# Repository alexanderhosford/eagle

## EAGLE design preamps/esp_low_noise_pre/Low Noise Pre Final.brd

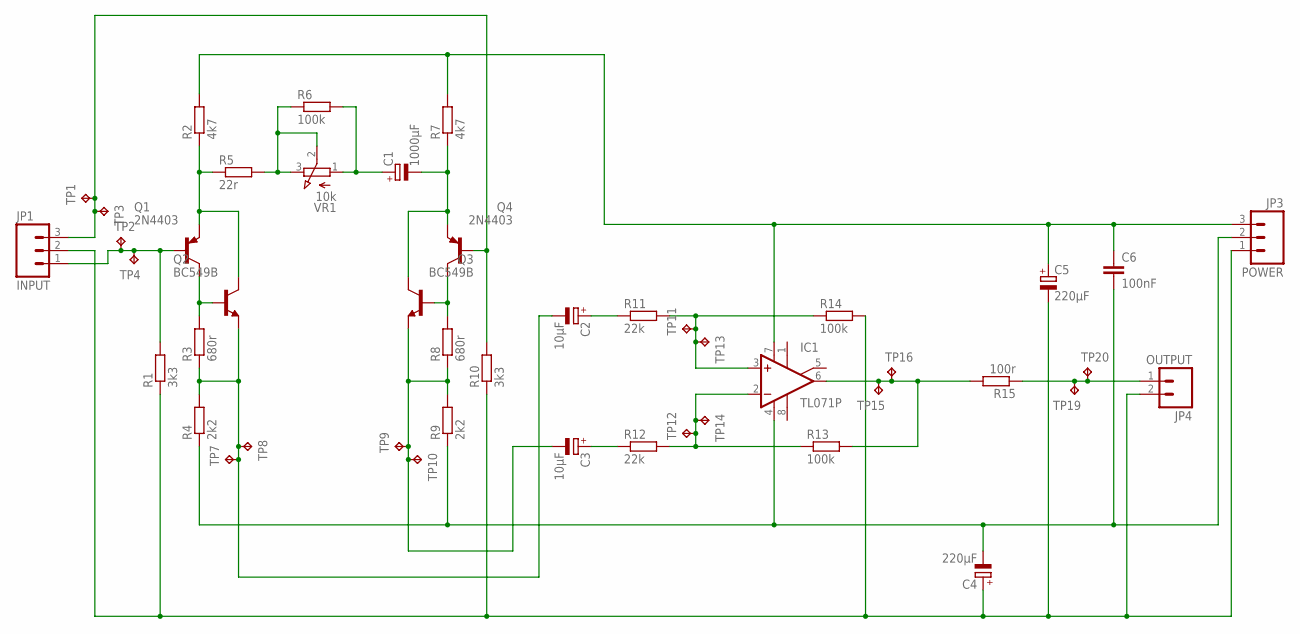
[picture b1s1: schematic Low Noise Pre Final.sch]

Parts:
C1: 1000µF; E5-10,5
C2, C3: 10µF; E15-5
C4, C5: 220µF; E5-10,5
C6: 100nF; C050-025X075
IC1: TL071P; DIL08
JP1: INPUT; SCREWTERMINAL-3.5MM-3
JP3: POWER; SCREWTERMINAL-3.5MM-3
JP4: OUTPUT; SCREWTERMINAL-3.5MM-2
Q1, Q4: 2N4403; TO92-BCE
Q2, Q3: BC549B; TO92-EBC
R1, R10: 3k3; 0207/7
R2, R7: 4k7; 0207/7
R3, R8: 680r; 0207/7
R4, R9: 2k2; 0207/7
R5: 22r; 0207/7
R6, R13, R14: 100k; 0207/7
R11, R12: 22k; 0207/7
R15: 100r; 0207/7
TP1, TP2, TP3, TP4, TP7, TP8, TP9, TP10, TP11, TP12, TP13, TP14, TP15, TP16, TP19, TP20: TPPAD1-13Y; P1-13Y
VR1: 10k; 3RP/1610N

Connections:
GND: C4.+, C5.-, JP1.2, JP3.1, JP4.2, R1.1, R10.1, R14.2
unnamed: C5.+, C6.1, IC1.7 (V+), JP3.3, R2.2, R7.2
unnamed: C4.-, C6.2, IC1.4 (V-), JP3.2, R4.1, R9.1
unnamed: JP4.1, R15.1, TP19.TP, TP20.TP
unnamed: IC1.6 (OUT), R13.2, R15.2, TP15.TP, TP16.TP
unnamed: IC1.2 (-IN), R12.2, R13.1, TP12.TP, TP14.TP
unnamed: IC1.3 (+IN), R11.2, R14.1, TP11.TP, TP13.TP
unnamed: C3.+, R12.1
unnamed: C2.+, R11.1
unnamed: C3.-, Q3.E, R8.1, R9.2, TP9.TP, TP10.TP
unnamed: Q1.C, Q2.B, R3.2
unnamed: C2.-, Q2.E, R3.1, R4.2, TP7.TP, TP8.TP
unnamed: Q3.B, Q4.C, R8.2
unnamed: JP1.3, Q4.B, R10.2, TP1.TP, TP3.TP
unnamed: JP1.1, Q1.B, R1.2, TP2.TP, TP4.TP
unnamed: Q1.E, Q2.C, R2.1, R5.1
unnamed: C1.-, Q3.C, Q4.E, R7.1
unnamed: R5.2, R6.1, VR1.2 (S), VR1.3 (E)
unnamed: C1.+, R6.2, VR1.1 (A)

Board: 2 copper layers, 46 parts (0 on the bottom side), 19 nets, no tracks yet.

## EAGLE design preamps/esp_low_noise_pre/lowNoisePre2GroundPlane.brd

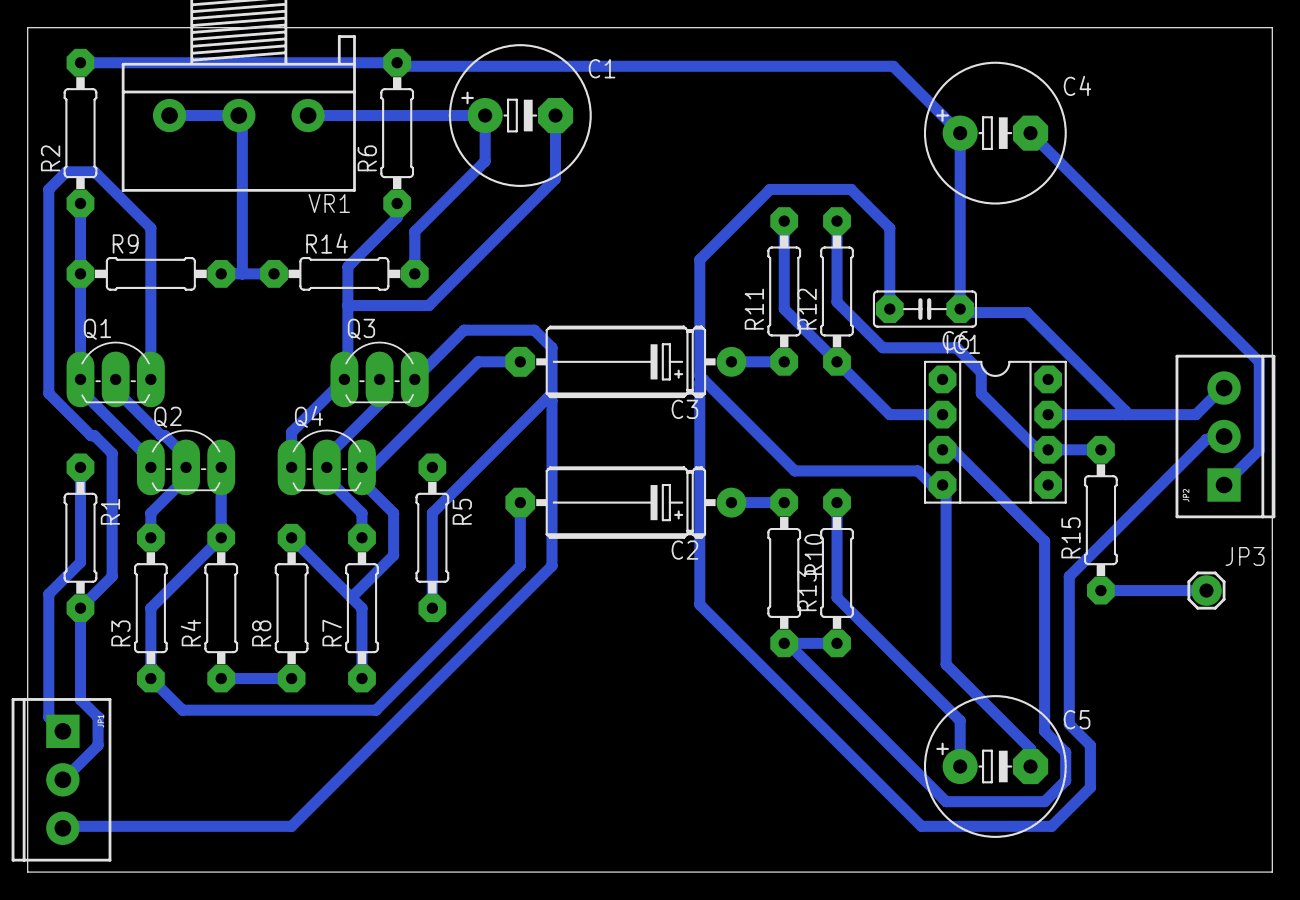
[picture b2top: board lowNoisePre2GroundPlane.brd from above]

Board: 2 copper layers, 89.8 x 60.9 mm, 30 parts (0 on the bottom side), 19 nets.

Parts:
C1: 1000µF; E5-10,5
C2, C3: 10µF; E15-5
C4, C5: 220µF; E5-10,5
C6: 100nF; C050-025X075
IC1: INA217P; DIL08
JP1: SCREWTERMINAL-3.5MM-3
JP2: POWER; SCREWTERMINAL-3.5MM-3
JP3: OUTPUT; 1X01
Q1: 2N4403; TO92-BCE
Q2, Q4: BC549B; TO92-EBC
Q3: BC369; TO92-BCE
R1, R5: 3k3; 0207/10
R2, R6: 4k7; 0207/10
R3, R7: 680r; 0207/10
R4, R8: 2k2; 0207/10
R9: 22r; 0207/10
R10, R11: 22k; 0207/10
R12, R13, R14: 100k; 0207/10
R15: 100r; 0207/10
VR1: 10k; 3RP/1610N

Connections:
GND: C4.-, C5.+, JP1.1, JP2.1, R1.1, R5.1, R13.2
unnamed: C4.+, C6.1, IC1.7, JP2.3, R2.2, R6.2
unnamed: C5.-, C6.2, IC1.4, JP2.2, R4.1, R8.1
unnamed: JP3.1, R15.1
unnamed: IC1.6, R12.2, R15.2
unnamed: IC1.2, R11.2, R12.1
unnamed: IC1.3, R10.2, R13.1
unnamed: C3.+, R11.1
unnamed: C2.+, R10.1
unnamed: C3.-, Q4.E, R7.1, R8.2
unnamed: Q1.C, Q2.B, R3.2
unnamed: C2.-, Q2.E, R3.1, R4.2
unnamed: Q3.C, Q4.B, R7.2
unnamed: JP1.3, Q3.B, R5.2
unnamed: JP1.2, Q1.B, R1.2
unnamed: Q1.E, Q2.C, R2.1, R9.1
unnamed: C1.-, Q3.E, Q4.C, R6.1
unnamed: R9.2, R14.1, VR1.2, VR1.3
unnamed: C1.+, R14.2, VR1.1

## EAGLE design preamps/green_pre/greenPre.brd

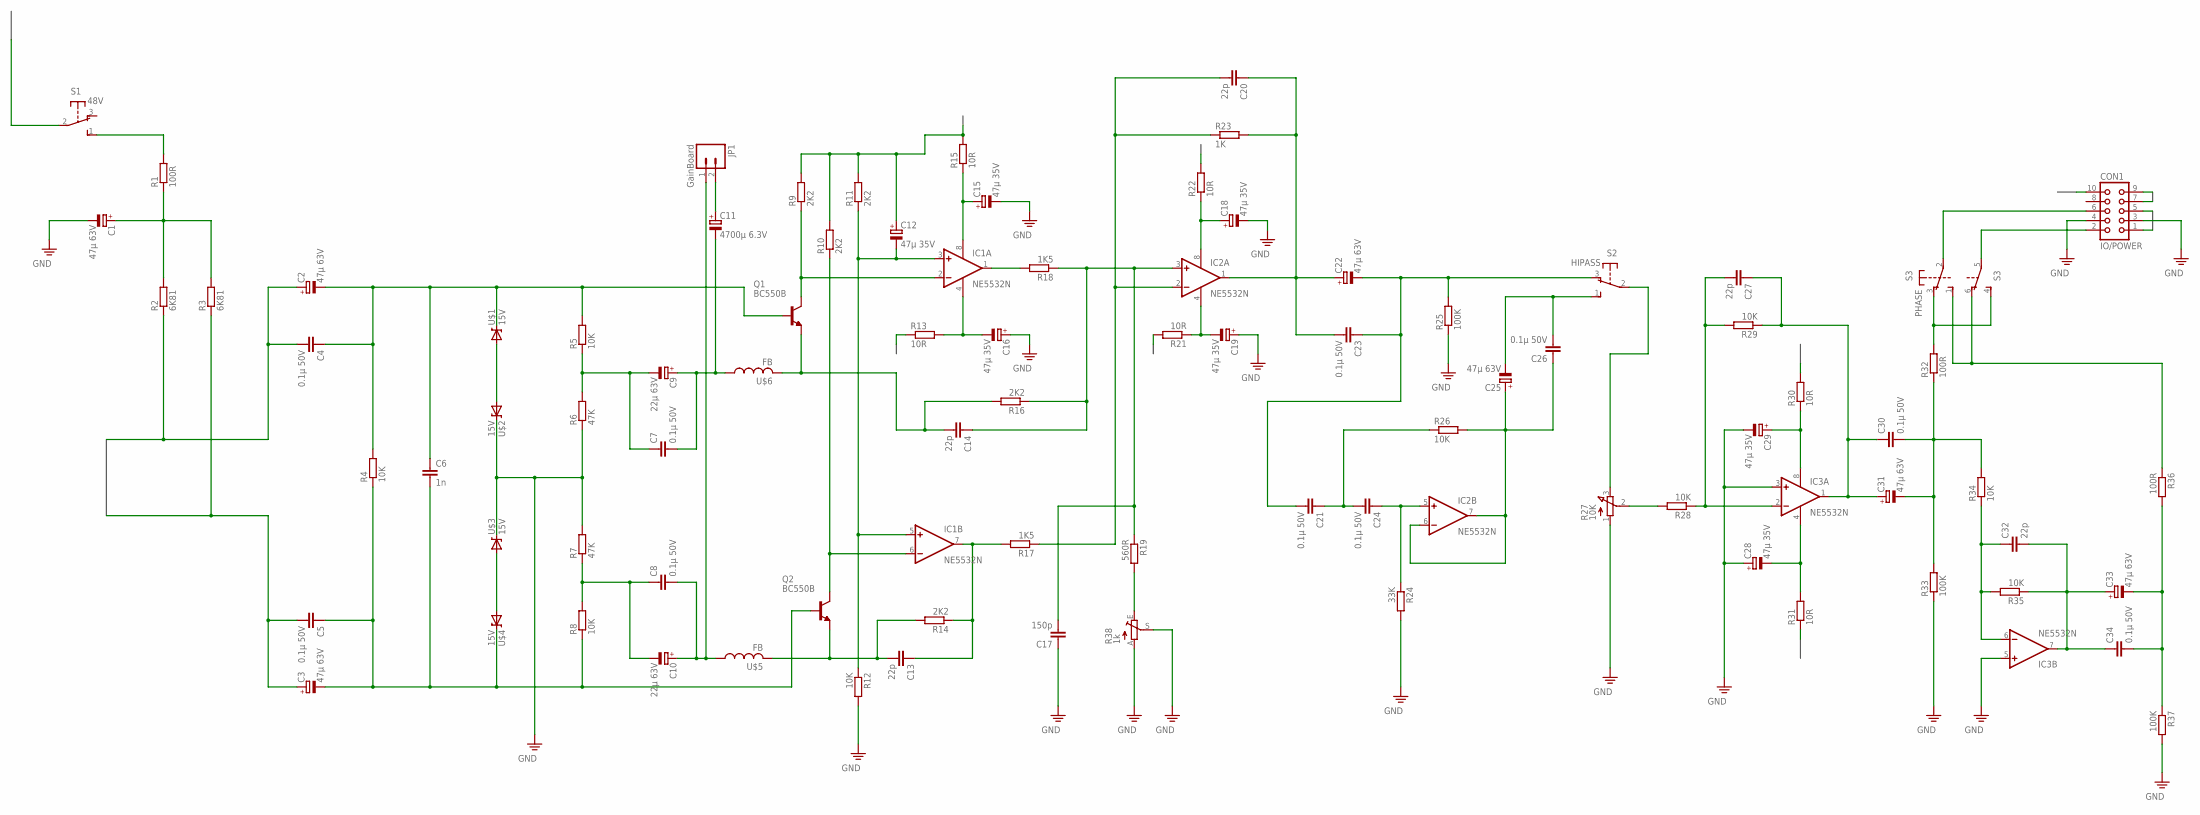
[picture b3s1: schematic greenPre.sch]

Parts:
C1, C2, C3, C22, C25, C31, C33: 47µ 63V; E2,5-5
C4, C5, C7, C8, C21, C23, C24, C26, C30, C34: 0.1µ 50V; C050-025X075
C6: 1n; C050-025X075
C9, C10: 22µ 63V; E2,5-5
C11: 4700µ 6.3V; E2,5-5
C12, C15, C16, C18, C19, C28, C29: 47µ 35V; E2,5-5
C13, C14, C20, C27, C32: 22p; C050-025X075
C17: 150p; C050-025X075
CON1: IO/POWER; CON10
IC1, IC2, IC3: NE5532N; DIL08
JP1: GainBoard; SCREWTERMINAL-3.5MM-2
Q1, Q2: BC550B; TO92-EBC
R1, R32, R36: 100R; 0207/10
R2, R3: 6K81; 0207/10
R4, R5, R8, R12, R26, R28, R29, R34, R35: 10K; 0207/10
R6, R7: 47K; 0207/10
R9, R10, R11, R14, R16: 2K2; 0207/10
R13, R15, R21, R22, R30, R31: 10R; 0207/10
R17, R18: 1K5; 0207/10
R19: 560R; 0207/10
R23: 1K; 0207/10
R24: 33K; 0207/10
R25, R33, R37: 100K; 0207/10
R27: 10K; 3RP/1610N
R38: 1k; B25P
S1: 48V; 9450-1
S2: HIPASS; 9450-1
S3: PHASE; 9450-2
U$1, U$2, U$3, U$4: 15V; DIODE-ZENER
U$5, U$6: FB

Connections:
15V1: C12.+, CON1.9, R9.2, R10.2, R11.2, R15.2, R22.2, R30.2
15V2: CON1.7, R13.1, R21.2, R31.1
48V: CON1.10, S1.2
GND: C1.-, C15.-, C16.+, C17.1, C18.-, C19.+, C28.+, C29.-, CON1.4, IC3.3 (+IN), IC3.5 (+IN), R6.1, R7.2, R12.2, R24.2, R25.1, R27.1 (A), R33.1, R37.2, R38.A, R38.S, U$2.P$1 (C), U$3.P$1 (C)
IN1: C2.+, C4.2, CON1.1, R2.1
IN2: C3.+, C5.2, CON1.5, R3.1
unnamed: C8.2, C10.+, JP1.1, U$5.P$1 (1)
unnamed: IC1.2 (-IN), Q1.C, R9.1
unnamed: C12.-, IC1.3 (+IN), IC1.5 (+IN), R11.1, R12.1
unnamed: IC1.6 (-IN), Q2.C, R10.1
unnamed: C14.2, Q1.E, R16.2, U$6.P$2 (2)
unnamed: C15.+, IC1.8 (V+), R15.1
unnamed: C16.-, IC1.4 (V-), R13.2
unnamed: IC1.1 (OUT), R18.2
unnamed: C7.1, C9.-, R5.1, R6.2
unnamed: C14.1, C17.2, IC2.3 (+IN), R16.1, R18.1, R19.1
unnamed: C7.2, C9.+, C11.-, U$6.P$1 (1)
unnamed: C20.2, IC2.2 (-IN), R17.1, R23.1
unnamed: C8.1, C10.-, R7.1, R8.2
unnamed: U$1.P$2 (A), U$2.P$2 (A)
unnamed: C11.+, JP1.2
unnamed: U$3.P$2 (A), U$4.P$2 (A)
unnamed: C18.+, IC2.8 (V+), R22.1
unnamed: C2.-, C4.1, C6.1, Q1.B, R4.2, R5.2, U$1.P$1 (C)
unnamed: C3.-, C5.1, C6.2, Q2.B, R4.1, R8.1, U$4.P$1 (C)
unnamed: C19.-, IC2.4 (V-), R21.1
unnamed: C20.1, C22.+, C23.2, IC2.1 (OUT), R23.2
unnamed: C21.2, C22.-, C23.1, R25.2, S2.3 (O)
unnamed: C24.1, IC2.5 (+IN), R24.1
unnamed: C13.2, Q2.E, R14.2, U$5.P$2 (2)
unnamed: C13.1, IC1.7 (OUT), R14.1, R17.2
unnamed: C21.1, C24.2, R26.1
unnamed: C25.+, C26.1, IC2.6 (-IN), IC2.7 (OUT), R26.2
unnamed: C25.-, C26.2, S2.1 (S)
unnamed: R27.3 (E), S2.2
unnamed: R19.2, R38.E
unnamed: R1.2, S1.1 (S)
unnamed: C1.+, R1.1, R2.2, R3.2
unnamed: R27.2 (S), R28.2
unnamed: C27.2, IC3.2 (-IN), R28.1, R29.2
unnamed: C27.1, C30.1, C31.+, IC3.1 (OUT), R29.1
unnamed: C28.-, IC3.4 (V-), R31.2
unnamed: C29.+, IC3.8 (V+), R30.1
unnamed: C30.2, C31.-, R32.1, R33.2, R34.2
unnamed: C32.1, IC3.6 (-IN), R34.1, R35.2
unnamed: C32.2, C33.+, C34.1, IC3.7 (OUT), R35.1
unnamed: C33.-, C34.2, R36.2, R37.1
unnamed: R32.2, S3.3 (O), S3.4 (S)
unnamed: R36.1, S3.1 (S), S3.6 (O)
unnamed: CON1.2, S3.5
unnamed: CON1.6, S3.2
PE: CON1.3

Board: 2 copper layers, 87 parts (0 on the bottom side), 51 nets, no tracks yet.

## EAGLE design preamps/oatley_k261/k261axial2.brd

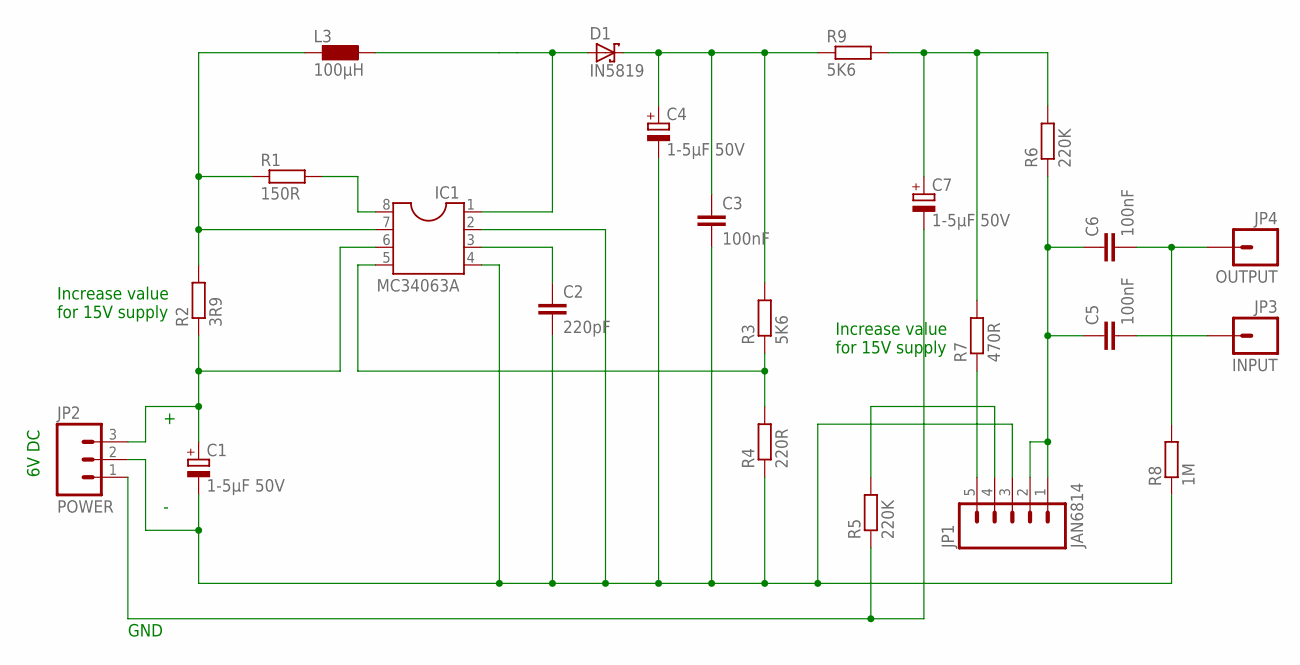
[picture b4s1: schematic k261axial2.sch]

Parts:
C1, C4, C7: 1-5µF 50V; E2,5-6E
C2: 220pF; C025-024X044
C3, C5, C6: 100nF; C050-025X075
D1: IN5819; DO41-7.6
IC1: MC34063A; SOCKET-08
JP1: JAN6814; 1X05_LONGPADS
JP2: POWER; SCREWTERMINAL-3.5MM-3
JP3: INPUT; 1X01
JP4: OUTPUT; 1X01
L3: 100µH; 0204/7
R1: 150R; 0207/7
R2: 3R9; 0207/7
R3, R9: 5K6; 0207/7
R4: 220R; 0207/7
R5, R6: 220K; 0207/7
R7: 470R; 0207/7
R8: 1M; 0207/7

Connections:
GND: C7.-, JP2.1, R5.1
unnamed: C7.+, R6.2, R7.2, R9.2
unnamed: IC1.8, R1.2
unnamed: D1.A, IC1.1, L3.1
unnamed: C1.+, IC1.6, JP2.3, R2.1
unnamed: C2.1, IC1.3
unnamed: C1.-, C2.2, C3.2, C4.-, IC1.2, IC1.4, JP1.3, JP2.2, R4.1, R8.1
unnamed: C5.1, C6.1, JP1.1, JP1.2, R6.1
unnamed: C6.2, JP4.1, R8.2
unnamed: C3.1, C4.+, D1.C, R3.2, R9.1
unnamed: C5.2, JP3.1
unnamed: JP1.5, R7.1
unnamed: JP1.4, R5.2
unnamed: IC1.7, L3.2, R1.1, R2.2
unnamed: IC1.5, R3.1, R4.2

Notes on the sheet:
GND
6V DC
Increase value for 15V supply

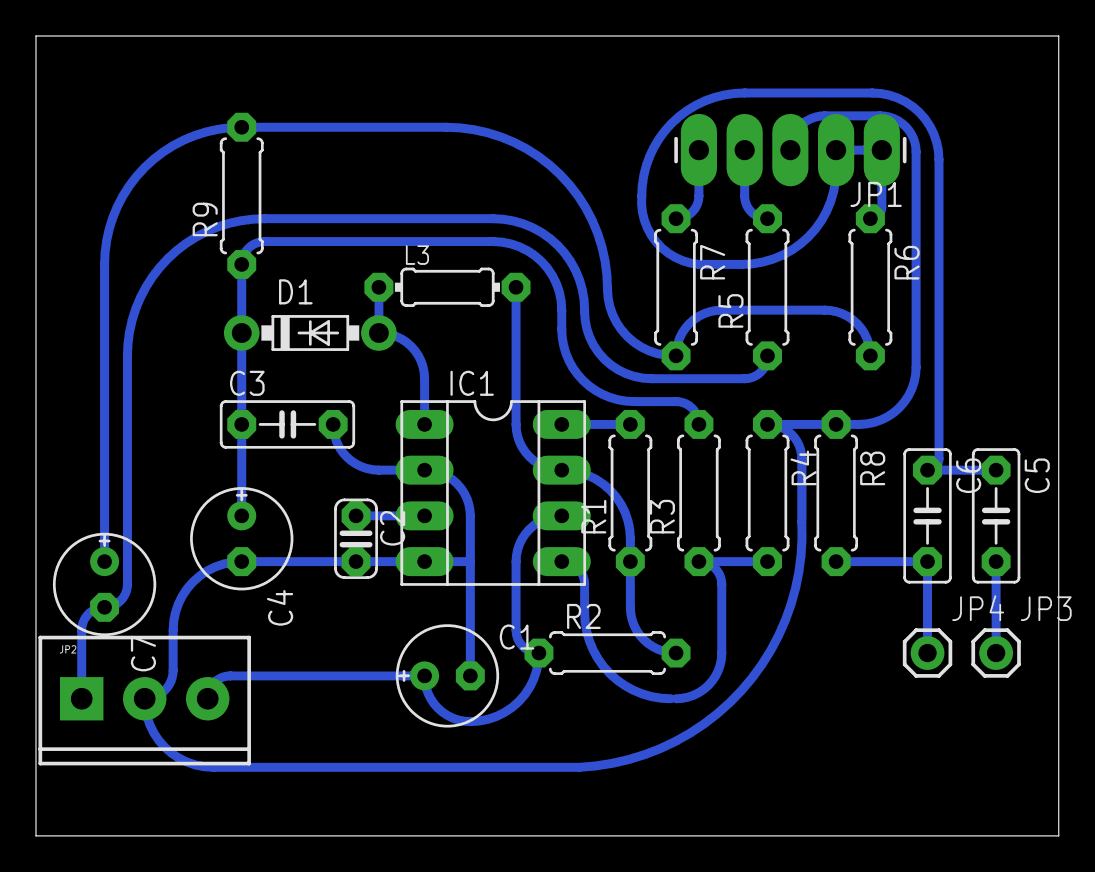
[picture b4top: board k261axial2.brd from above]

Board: 2 copper layers, 56.8 x 44.4 mm, 23 parts (0 on the bottom side), 15 nets.

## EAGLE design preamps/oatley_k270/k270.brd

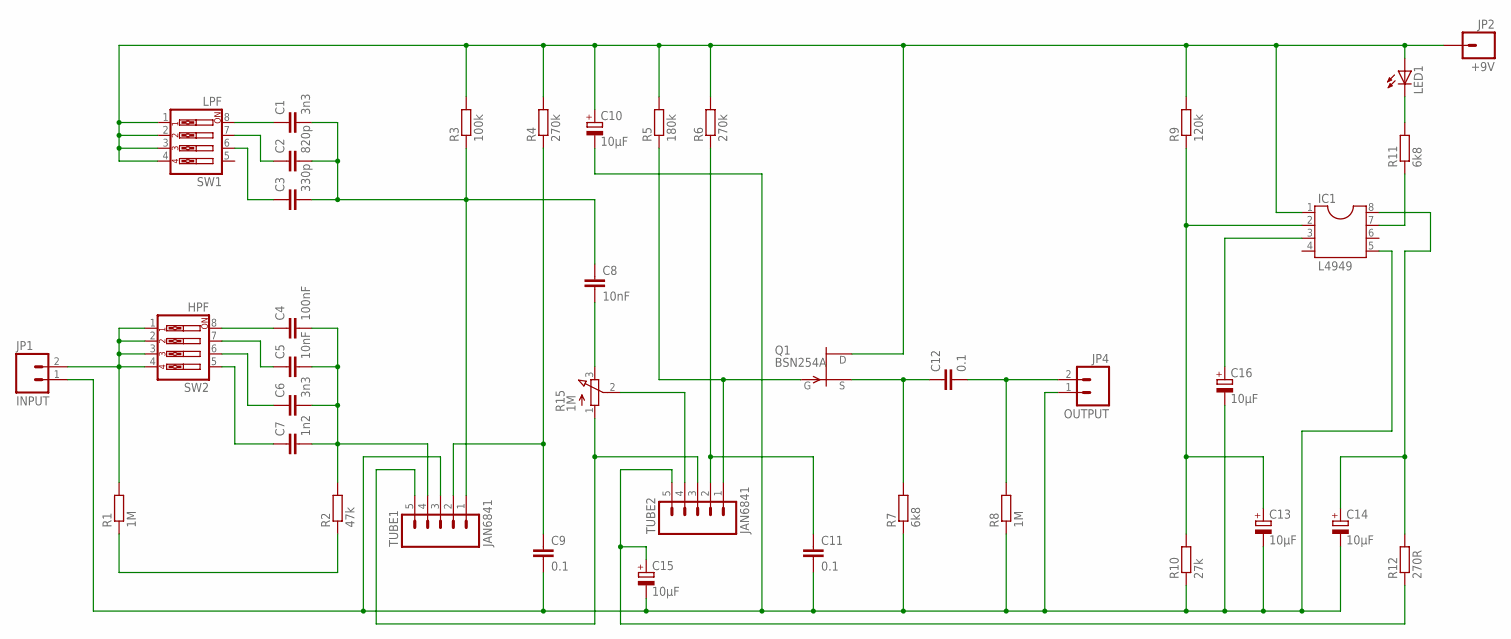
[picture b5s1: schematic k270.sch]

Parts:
C1, C6: 3n3; C050-024X044
C2: 820p; C050-024X044
C3: 330p; C050-024X044
C4: 100nF; C050-024X044
C5, C8: 10nF; C050-024X044
C7: 1n2; C050-024X044
C9, C11, C12: 0.1; C050-024X044
C10, C13, C14, C15, C16: 10µF; E2,5-6E
IC1: L4949; SOCKET-08
JP1: INPUT; SCREWTERMINAL-3.5MM-2
JP2: +9V; 1X01_LONGPAD
JP4: OUTPUT; SCREWTERMINAL-3.5MM-2
LED1: LED5MM
Q1: BSN254A; TO92
R1, R8: 1M; 0207/10
R2: 47k; 0207/10
R3: 100k; 0207/10
R4, R6: 270k; 0207/10
R5: 180k; 0207/10
R7, R11: 6k8; 0207/10
R9: 120k; 0207/10
R10: 27k; 0207/10
R12: 270R; 0207/10
R15: 1M; 3RP/1610N
SW1: LPF; EDG-04
SW2: HPF; EDG-04
TUBE1, TUBE2: JAN6841; 1X05_LONGPADS

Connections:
GND: C9.2, C10.-, C11.2, C13.-, C14.-, C15.-, C16.-, IC1.5, JP1.1, JP4.1, R7.1, R8.1, R10.1, TUBE1.3
unnamed: C1.1, SW1.8
unnamed: C2.1, SW1.7
unnamed: C3.1, SW1.6
unnamed: C1.2, C2.2, C3.2, C8.1, R3.1, TUBE1.1
unnamed: C4.1, SW2.8
unnamed: C5.1, SW2.7
unnamed: C6.1, SW2.6
unnamed: C7.1, SW2.5
unnamed: C4.2, C5.2, C6.2, C7.2, R2.2, TUBE1.4
unnamed: JP1.2, R1.2, SW2.1, SW2.2, SW2.3, SW2.4
unnamed: R1.1, R2.1
unnamed: C10.+, IC1.1, JP2.1, LED1.A, Q1.1 (D), R3.2, R4.2, R5.2, R6.2, R9.2, SW1.1, SW1.2, SW1.3, SW1.4
unnamed: C9.1, R4.1, TUBE1.2
unnamed: C8.2, R15.3 (E)
unnamed: R15.2 (S), TUBE2.4
unnamed: C11.1, R6.1, TUBE2.2
unnamed: R15.1 (A), TUBE1.5, TUBE2.3
unnamed: C15.+, R12.1, TUBE2.5
unnamed: Q1.2 (G), R5.1, TUBE2.1
unnamed: C12.1, Q1.3 (S), R7.2
unnamed: C12.2, JP4.2, R8.2
unnamed: C13.+, IC1.2, R9.1, R10.2
unnamed: C16.+, IC1.3
unnamed: IC1.7, R11.1
unnamed: LED1.K (C), R11.2
unnamed: C14.+, IC1.8, R12.2

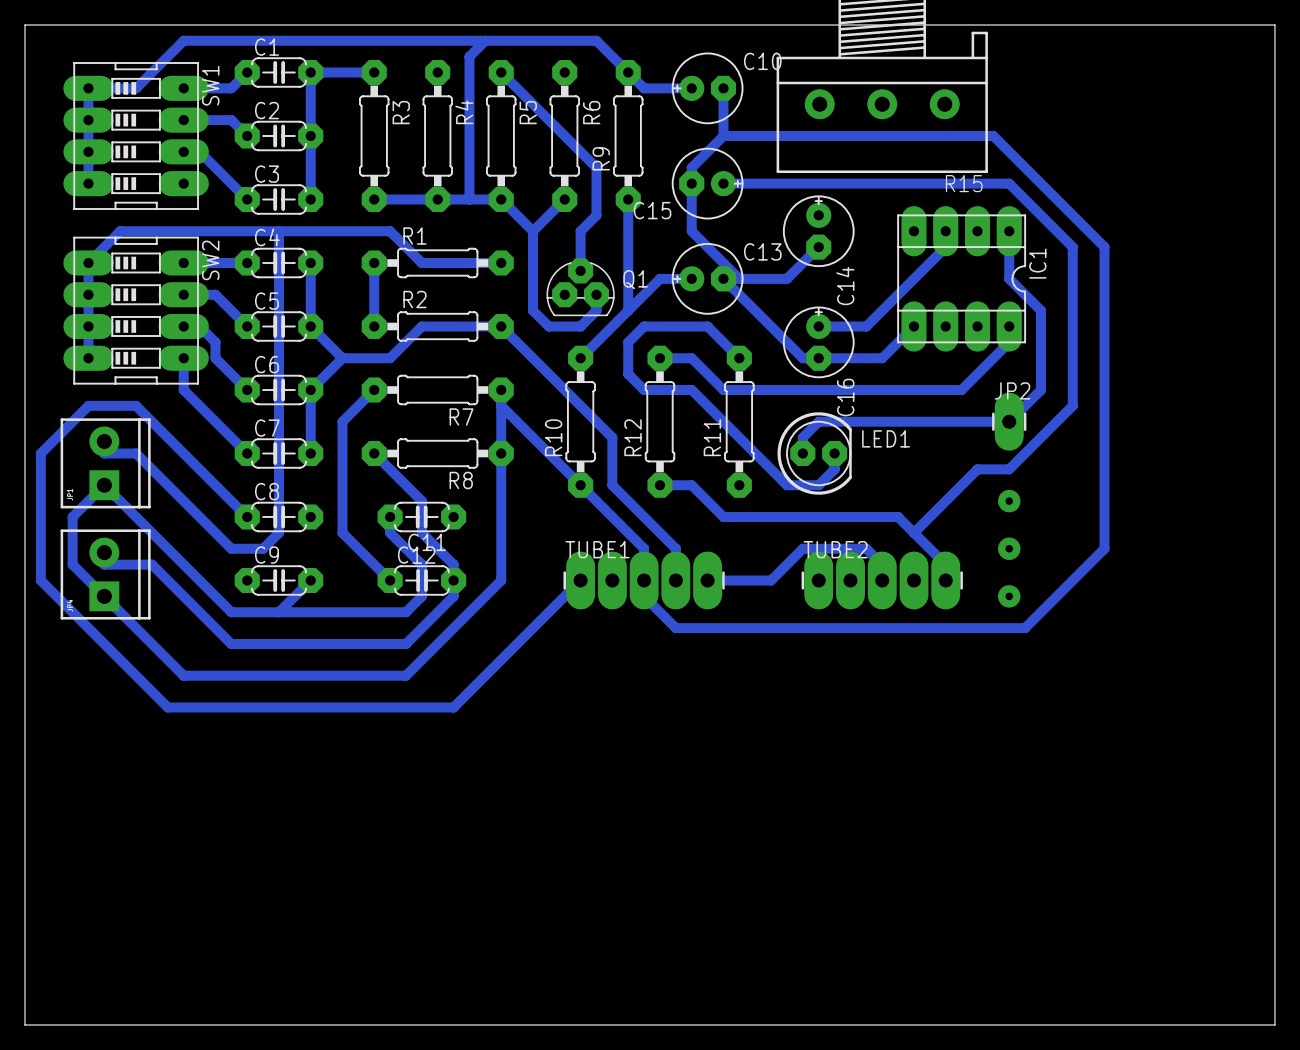
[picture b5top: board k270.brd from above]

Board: 2 copper layers, 100.0 x 80.0 mm, 39 parts (0 on the bottom side), 27 nets.

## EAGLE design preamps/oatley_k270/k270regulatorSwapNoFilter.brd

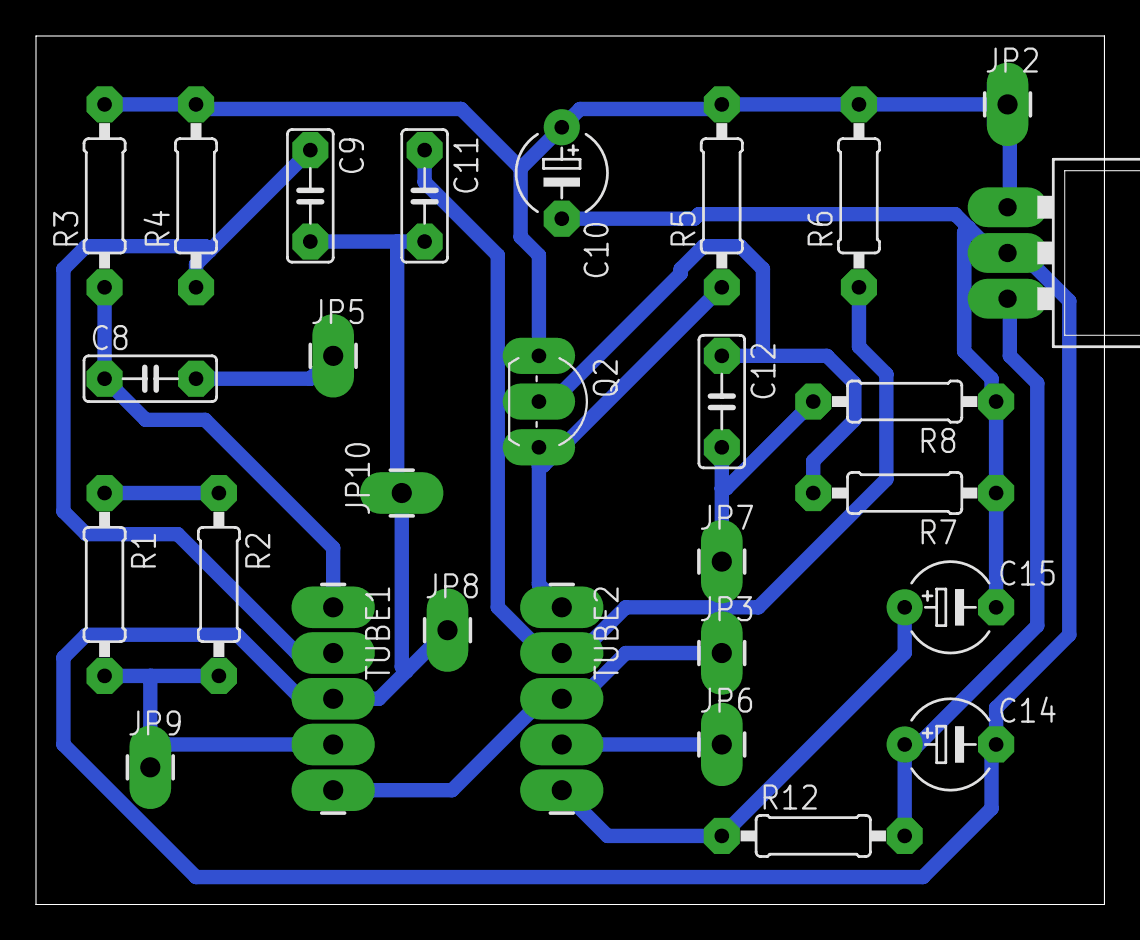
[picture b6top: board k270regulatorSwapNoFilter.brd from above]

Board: 2 copper layers, 59.4 x 48.2 mm, 28 parts (0 on the bottom side), 15 nets.

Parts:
C8: 10nF; C050-025X075
C9, C11, C12: 0.1; C050-025X075
C10, C14, C15: 10µF; E5-5
IC2: 78XXL
JP2: +9V; 1X01_LONGPAD
JP3: pot1; 1X01_LONGPAD
JP5: pot3; 1X01_LONGPAD
JP6: potWiper; 1X01_LONGPAD
JP7: OUT.SIG; 1X01_LONGPAD
JP8: OUT.GND; 1X01_LONGPAD
JP9: IN.SIG; 1X01_LONGPAD
JP10: IN.GND; 1X01_LONGPAD
Q2: BSN254A; TO92-
R1, R8: 1M; 0207/10
R2: 47k; 0207/10
R3: 100k; 0207/10
R4, R6: 270k; 0207/10
R5: 180k; 0207/10
R7: 6k8; 0207/10
R12: 270R; 0207/10
TUBE1, TUBE2: JAN6841; 1X05_LONGPADS

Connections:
5V: C14.+, IC2.OUT, R12.2
9V: C10.+, IC2.IN, JP2.1, Q2.3, R3.2, R4.2, R5.2, R6.2
GND: C9.2, C10.-, C11.2, C14.-, C15.-, IC2.GND, JP8.1, JP10.1, R7.1, R8.1, TUBE1.3
unnamed: JP9.1, R1.2, R2.2, TUBE1.4
unnamed: C8.1, R3.1, TUBE1.1
unnamed: R1.1, R2.1
unnamed: C8.2, JP5.1
unnamed: C9.1, R4.1, TUBE1.2
unnamed: JP6.1, TUBE2.4
unnamed: C11.1, R6.1, TUBE2.2
unnamed: JP3.1, TUBE1.5, TUBE2.3
unnamed: C15.+, R12.1, TUBE2.5
unnamed: Q2.1, R5.1, TUBE2.1
unnamed: C12.1, Q2.2, R7.2
unnamed: C12.2, JP7.1, R8.2

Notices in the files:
parts and their libraries:
SparkFun: Licensing: CC v3.0 Share-Alike You are welcome to use this library for commercial purposes.
